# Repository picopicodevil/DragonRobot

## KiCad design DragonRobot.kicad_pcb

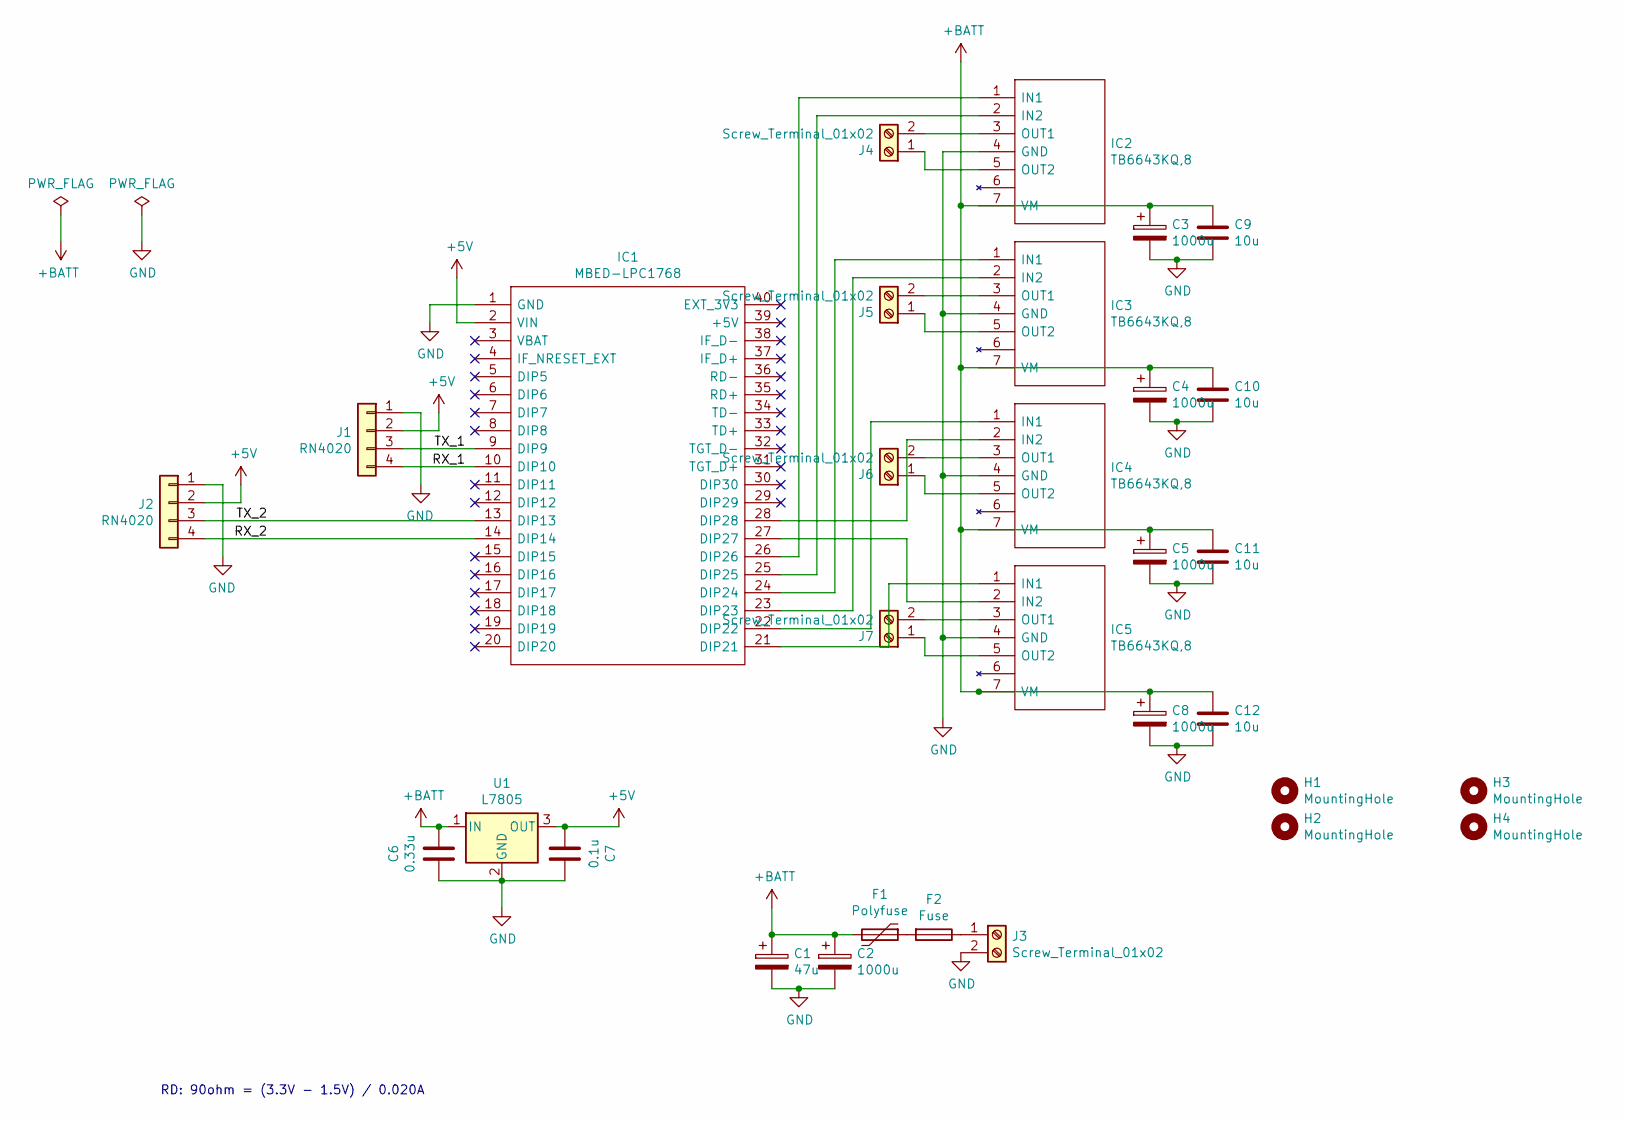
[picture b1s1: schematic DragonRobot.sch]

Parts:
C1: 47u; CP_Radial_D5.0mm_P2.50mm
C2, C3, C4, C5, C8: 1000u; CP_Radial_D10.0mm_P5.00mm
C6: 0.33u; C_Disc_D3.0mm_W1.6mm_P2.50mm
C7: 0.1u; C_Disc_D3.0mm_W1.6mm_P2.50mm
C9, C10, C11, C12: 10u; C_Disc_D3.0mm_W1.6mm_P2.50mm
F1: Polyfuse; Fuse_Littelfuse_395Series
F2: Fuse; MF505
H1, H2, H3, H4: MountingHole; MountingHole_3.2mm_M3
IC1: MBED-LPC1768; DIPS2286W63P254L5370H300Q40N; Manufacturer_Part_Number MBED-LPC1768
IC2, IC3, IC4, IC5: TB6643KQ,8; HSIP7-P-2.54A; Manufacturer_Part_Number TB6643KQ,8; Mouser Part Number 757-TB6643KQ8
J1, J2: RN4020; PinHeader_1x04_P2.54mm_Vertical
J3: Screw_Terminal_01x02; TerminalBlock_bornier-2_P5.08mm
J4, J5, J6, J7: Screw_Terminal_01x02; AMASS_XT60-M_1x02_P7.20mm_Vertical
U1: L7805; TO-220-3_Vertical

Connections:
+5V: C7.2, IC1.2 (VIN), J1.2, J2.2, U1.3 (OUT)
+BATT: C1.1, C2.1, C3.1, C4.1, C5.1, C6.1, C8.1, C9.1, C10.1, C11.1, C12.1, F1.2, IC2.7 (VM), IC3.7 (VM), IC4.7 (VM), IC5.7 (VM), U1.1 (IN)
/RX_1: IC1.10 (DIP10), J1.4
/RX_2: IC1.14 (DIP14), J2.4
/TX_1: IC1.9 (DIP9), J1.3
/TX_2: IC1.13 (DIP13), J2.3
GND: C1.2, C2.2, C3.2, C4.2, C5.2, C6.2, C7.1, C8.2, C9.2, C10.2, C11.2, C12.2, IC1.1 (GND), IC2.4 (GND), IC3.4 (GND), IC4.4 (GND), IC5.4 (GND), J1.1, J2.1, J3.2, U1.2 (GND)
unnamed: F1.1, F2.2
unnamed: F2.1, J3.1
unnamed: IC1.21 (DIP21), IC5.1 (IN1)
unnamed: IC1.22 (DIP22), IC4.1 (IN1)
unnamed: IC1.23 (DIP23), IC3.2 (IN2)
unnamed: IC1.24 (DIP24), IC3.1 (IN1)
unnamed: IC1.25 (DIP25), IC2.2 (IN2)
unnamed: IC1.26 (DIP26), IC2.1 (IN1)
unnamed: IC1.27 (DIP27), IC5.2 (IN2)
unnamed: IC1.28 (DIP28), IC4.2 (IN2)
unnamed: IC2.3 (OUT1), J4.2
unnamed: IC2.5 (OUT2), J4.1
unnamed: IC3.3 (OUT1), J5.2
unnamed: IC3.5 (OUT2), J5.1
unnamed: IC4.3 (OUT1), J6.2
unnamed: IC4.5 (OUT2), J6.1
unnamed: IC5.3 (OUT1), J7.2
unnamed: IC5.5 (OUT2), J7.1

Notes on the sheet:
RD: 90ohm = (3.3V - 1.5V) / 0.020A

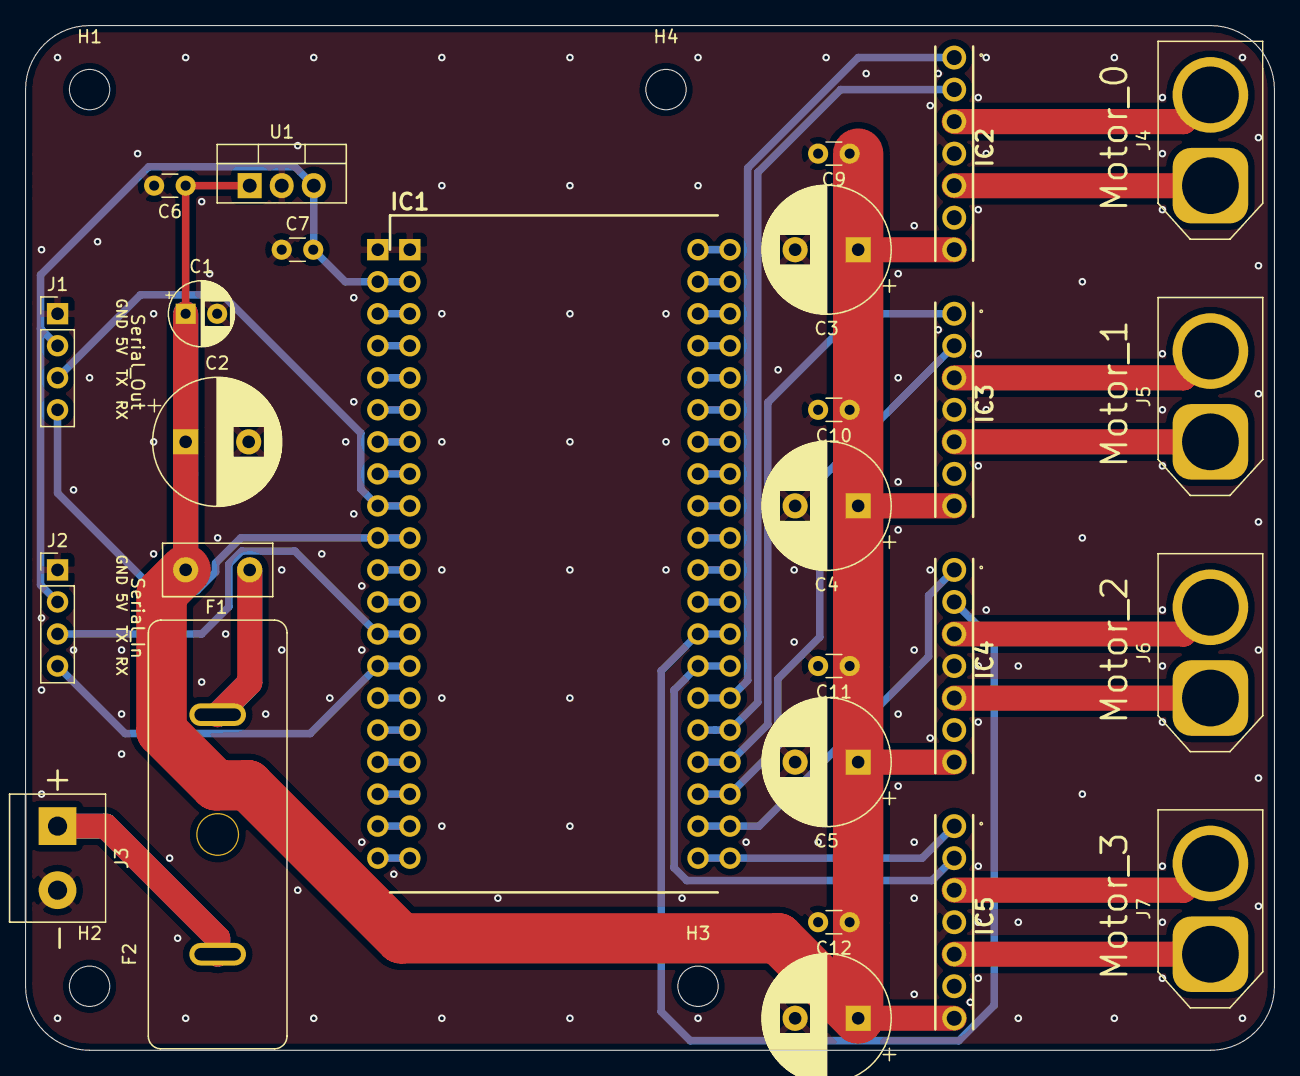
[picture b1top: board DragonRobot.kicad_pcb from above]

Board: 2 copper layers, 99.1 x 81.3 mm, 31 parts (0 on the bottom side), 25 nets.

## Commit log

2020-09-17 order Version 1.0
    order to elecrow
